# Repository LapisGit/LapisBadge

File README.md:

# LapisBadge
Open-Source "hackbadge" for Hack Club's Highway.

This serves as a way to learn my name, or for myself to cycle through and check the time, weather, etc.

It allows for talking to people to start and continue much faster, and that is especially needed if I go to Undercity.

Also very much based off of the [HackPad](https://hackpad.hackclub.com) case, it was perfect for this use case, and I was already familiar with it, so why the hell not!

## But Lapis, how did you come up with this?!?
I was scrolling through the Highway site, just as I submitted my HackPad, and I saw the "Hack Badge" idea listed, and I wondered, "what the hell is a hack badge??" so I found the images provided, and holy crap they look cool. So I decided, if I'm actually going to be going to Undercity, why not go in style!!

# CAD:

# PCB:

# Firmware:

*(untested and unfinished, will stay that way until i can actually test on hardware lol)*

# BOM:
| Product Name            | Price                            | Quantity | Store Page                                                                                                                                                                                                                       |
|-------------------------|----------------------------------|----------|----------------------------------------------------------------------------------------------------------------------------------------------------------------------------------------------------------------------------------|
| 0.91in OLED Display     | $1.68                            | 1        | [Aliexpress](https://www.aliexpress.us/item/3256808211699975.html?isdl=y&albch=shopping&acnt=135095331&albcp=555220768&albag=1309519513086509&slnk=&trgt=pla-2333644710812054&plac=&crea=81845026508678&netw=s&device=c&mtctp=e) |
| Seeed XIAO RP2040       | $7.32                            | 1        | [Aliexpress](https://www.aliexpress.us/item/3256808014602728.html?isdl=y&albch=shopping&acnt=135095331&albcp=555220768&albag=1309519513086509&slnk=&trgt=pla-2333644710812054&plac=&crea=81845026508678&netw=s&device=c&mtctp=e) |
| PCB                     | $10.04 (calculated with gerbers) | 1        | [PCBWay (Global Standard Shipping)](https://www.pcbway.com/)                                                                                                                                                                     |
| Case                    | $9.96                            | 1        | [PCBWay](https://www.pcbway.com/)                                                                                                                                                                                                |
| Blank DSA Keycap        | $1.75                            | 1        | [Aliexpress](https://www.aliexpress.us/item/3256807965011039.html?isdl=y&albch=shopping&acnt=135095331&albcp=554961410&albag=1299623884422788&slnk=&trgt=pla-4584826057675486&plac=&crea=81226547867988&netw=s&device=c&mtctp=e) |
| MX-Style switch         | $0.99                            | 1        | [Aliexpress](https://www.aliexpress.us/item/3256802192387196.html?utparam-url=scene%3Asearch%7Cquery_from%3A&search_p4p_id=20250629063600799914169269810002253870_1)                                                             |
| M3x16mm Screws          | $3.20                            | 1        | [Aliexpress](https://www.aliexpress.us/item/2251832655084301.html?productId=2251832655084301)                                                                                                                                    |
| Estimated Overall Price | ~35$                             | N/A      | N/A                                                                                                                                                                                                                              |

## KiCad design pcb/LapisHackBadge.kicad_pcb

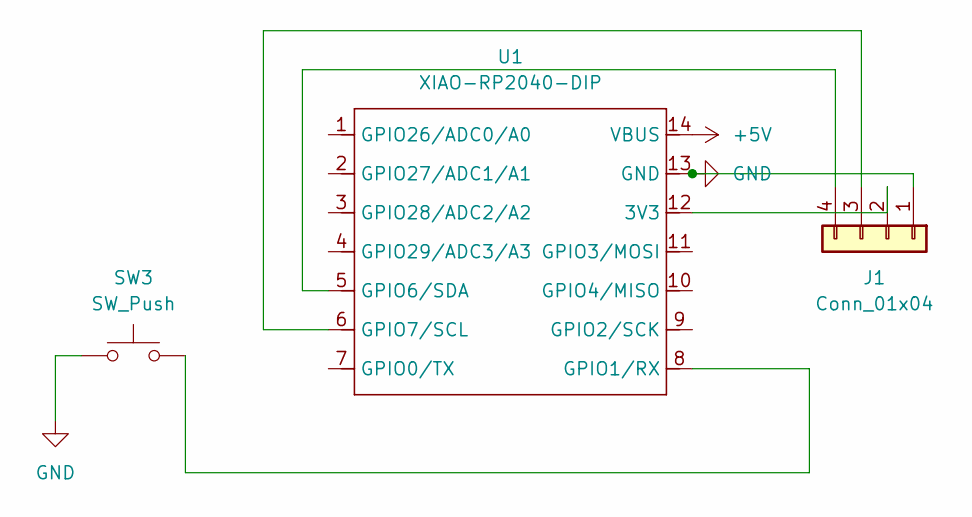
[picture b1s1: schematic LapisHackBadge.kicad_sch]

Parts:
J1: Conn_01x04; SSD1306-0.91-OLED-4pin-128x32
SW3: SW_Push; SW_Cherry_MX_1.00u_PCB
U1: XIAO-RP2040-DIP

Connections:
+5V: U1.14 (VBUS)
GND: J1.1, SW3.1, U1.13 (GND)
unnamed: J1.2, U1.12 (3V3)
unnamed: J1.3, U1.6 (GPIO7/SCL)
unnamed: J1.4, U1.5 (GPIO6/SDA)
unnamed: SW3.2, U1.8 (GPIO1/RX)

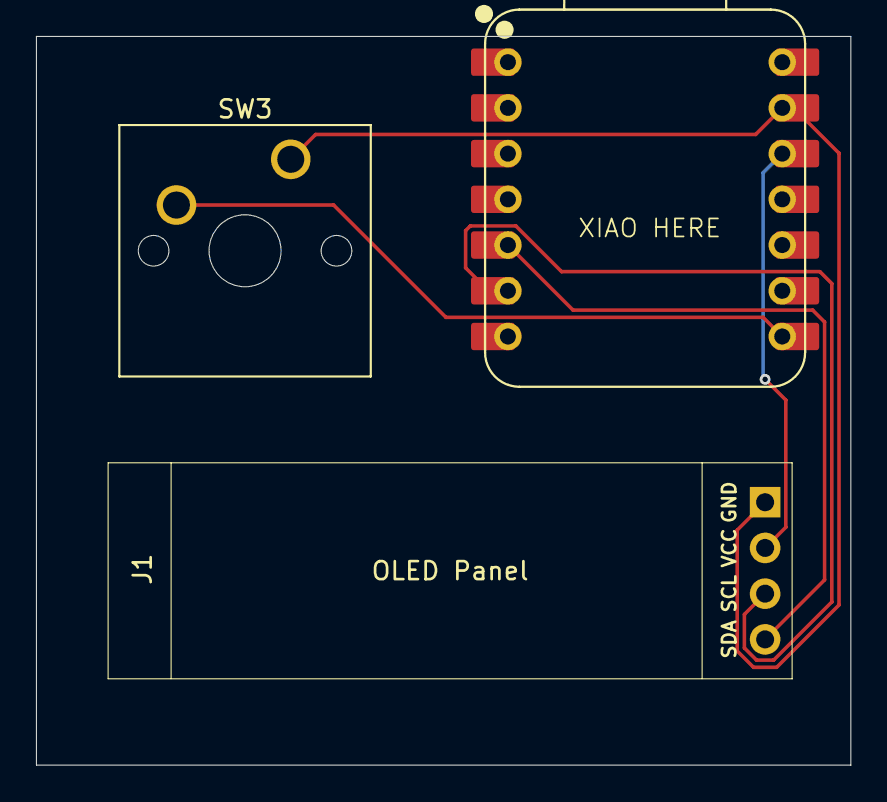
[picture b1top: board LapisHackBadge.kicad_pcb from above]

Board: 2 copper layers, 45.2 x 40.5 mm, 3 parts (0 on the bottom side), 5 nets.

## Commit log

2025-06-28 aaaaaa
2025-06-28 add bom
2025-06-29 ready for prod
2025-06-29 add BOM csv
